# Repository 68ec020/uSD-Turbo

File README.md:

# BBC Micro TurboMMC Interface

Use with
https://github.com/hoglet67/MMFS

Inspired by
http://stardot.org.uk/forums/viewtopic.php?t=9445&f=3#p110691

The interface works in my BBC Micro. I included resisters everywhere two outputs could be active at the same time, like in the hand-drawn schematic. So it should be safe. But: Use at your own risk!

## Changes compared to the hand-drawn schematic

* active level shifters (74LVC125AD) instead of voltage dividers
* 3.3 V voltage regulator
* no pull-ups on PB2, PB3, PB4, marked with VDD ? in the hand-drawn schematic (maybe I should add them, if the port is configured as input)

## Build your own

I ordered PCBs from JLCPCB. Just use the file jlcpcb/production_files/GERBER-uSD-Turbo.zip

Use the HTML-based BOM tool in /bom

I bought a microSD card slot on eBay, but I don't have a specific part number.

Make sure the right angle connector is mounted like in the 2D rendering. Pin 1 is the sqare pad. Make sure this corresponds with pin 1 of your port!

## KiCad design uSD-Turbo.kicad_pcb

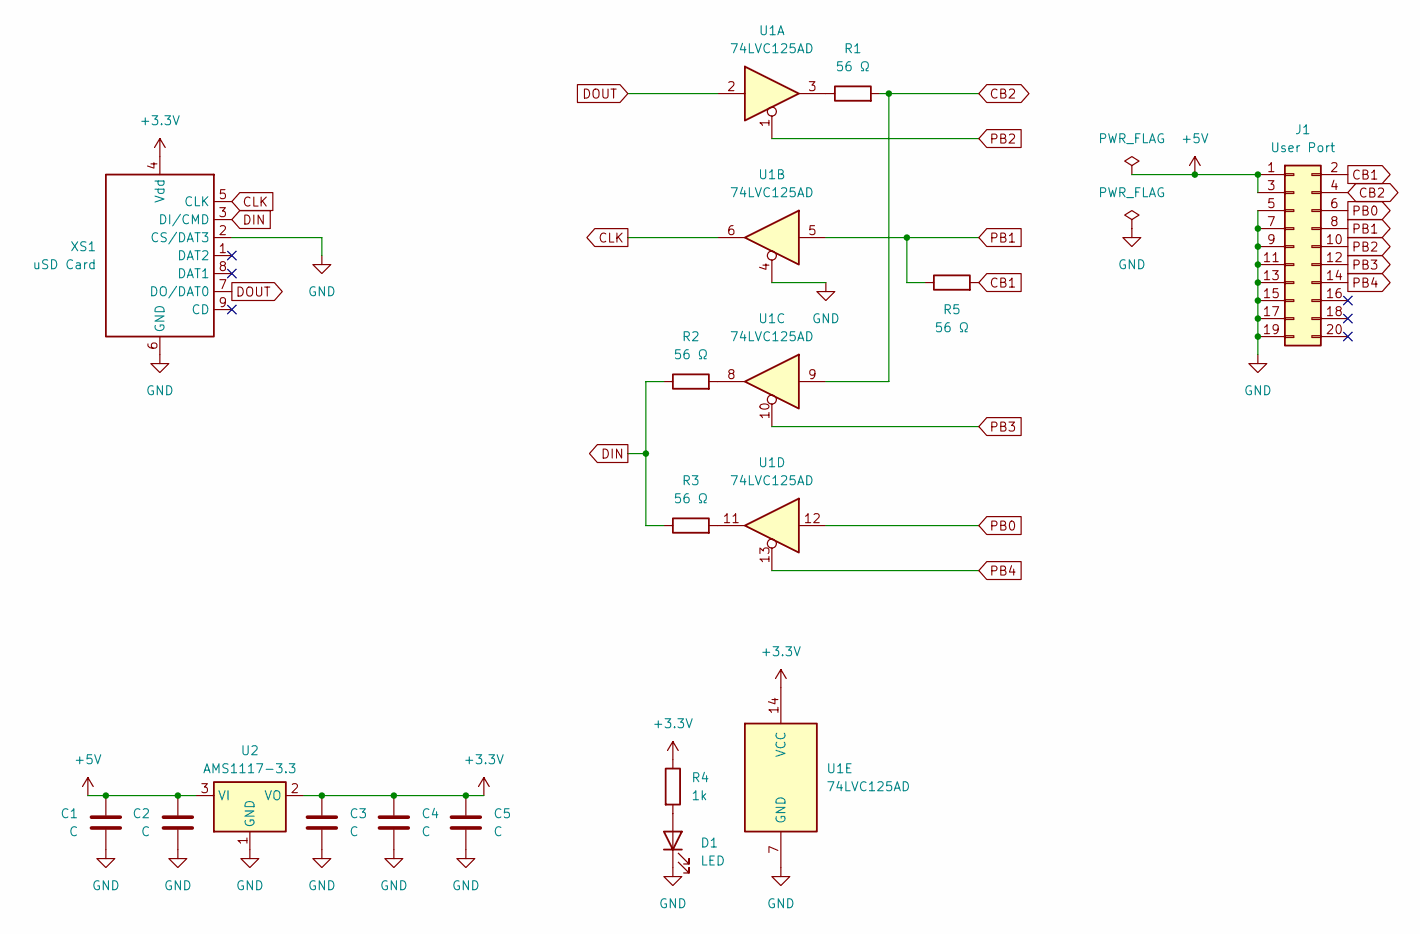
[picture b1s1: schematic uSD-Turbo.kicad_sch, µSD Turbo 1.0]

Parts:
C1, C2, C3, C4, C5: C; C_0603_1608Metric
D1: LED; LED_0603_1608Metric
J1: User Port; PinSocket_2x10_P2.54mm_Horizontal
R1, R2, R3, R5: 56 Ω; R_0603_1608Metric
R4: 1k; R_0603_1608Metric
U1: 74LVC125AD; SOIC-14_3.9x8.7mm_P1.27mm
U2: AMS1117-3.3; SOT-223-3_TabPin2
XS1: uSD Card; Conn_uSDcard

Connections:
+3.3V: C3.1, C4.1, C5.1, R4.1, U1.14 (VCC), U2.2 (VO), XS1.4 (Vdd)
+5V: C1.1, C2.1, J1.1, J1.3, U2.3 (VI)
CB1: J1.2, R5.2
CB2: J1.4, R1.2, U1.9
CLK: U1.6, XS1.5 (CLK)
DIN: R2.1, R3.1, XS1.3 (DI/CMD)
DOUT: U1.2, XS1.7 (DO/DAT0)
GND: C1.2, C2.2, C3.2, C4.2, C5.2, D1.1 (K), J1.5, J1.7, J1.9, J1.11, J1.13, J1.15, J1.17, J1.19, U1.4, U1.7 (GND), U2.1 (GND), XS1.2 (CS/DAT3), XS1.6 (GND)
unnamed: D1.2 (A), R4.2
unnamed: R1.1, U1.3
unnamed: R2.2, U1.8
unnamed: R3.2, U1.11
PB0: J1.6, U1.12
PB1: J1.8, R5.1, U1.5
PB2: J1.10, U1.1
PB3: J1.12, U1.10
PB4: J1.14, U1.13

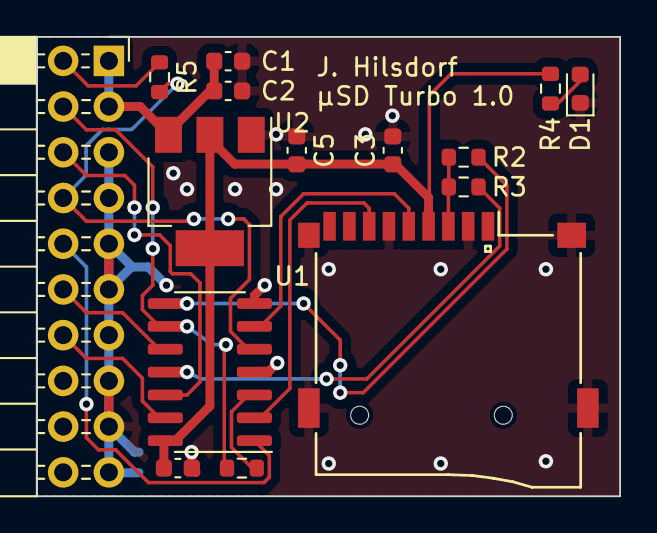
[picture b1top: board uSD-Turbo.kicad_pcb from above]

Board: 2 copper layers, 32.4 x 25.5 mm, 15 parts (0 on the bottom side), 17 nets.

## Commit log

2023-08-18 Renamed project, added resistor between PB1 and CB1, added BOM and Gerber files
2023-08-18 Added GPLv2 license
